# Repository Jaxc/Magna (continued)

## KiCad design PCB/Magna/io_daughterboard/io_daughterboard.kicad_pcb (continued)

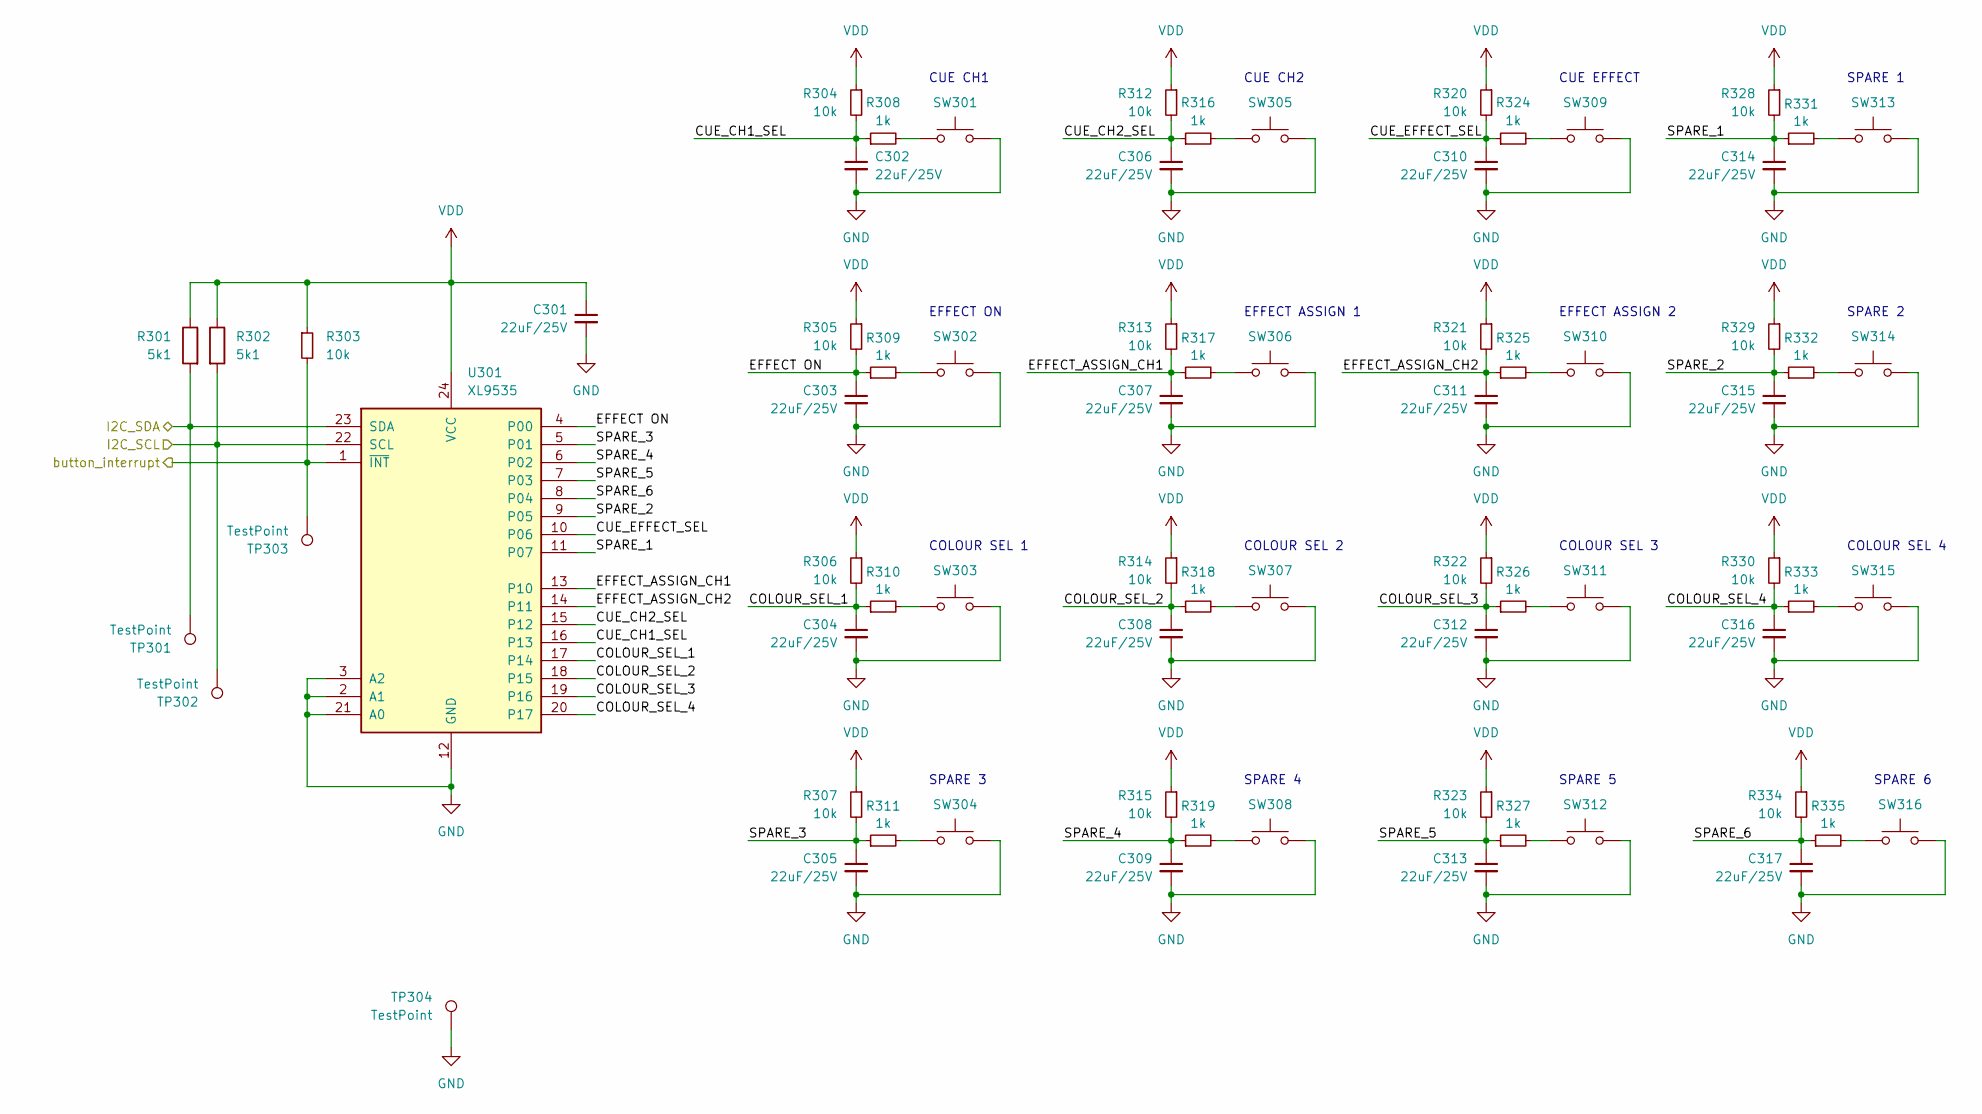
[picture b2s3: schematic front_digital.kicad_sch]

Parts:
C301, C302, C303, C304, C305, C306, C307, C308, C309, C310, C311, C312, C313, C314, C315, C316, C317: 22uF/25V; C_0805_2012Metric_Pad1.18x1.45mm_HandSolder; LCSC C45783
R301, R302: 5k1; R_0805_2012Metric_Pad1.20x1.40mm_HandSolder; LCSC C218638
R303, R304, R305, R306, R307, R312, R313, R314, R315, R320, R321, R322, R323, R328, R329, R330, R334: 10k; R_0805_2012Metric_Pad1.20x1.40mm_HandSolder; LCSC C17414
R308, R309, R310, R311, R316, R317, R318, R319, R324, R325, R326, R327, R331, R332, R333, R335: 1k; R_0805_2012Metric_Pad1.20x1.40mm_HandSolder; LCSC C17513
SW301, SW302, SW303, SW304, SW305, SW306, SW307, SW308, SW309, SW310, SW311, SW312, SW313, SW314, SW315, SW316: SW_Push_1P1T_XKB_TS-1187A; LCSC C318884
TP301, TP302, TP303, TP304: TestPoint; TestPoint_Keystone_5000-5004_Miniature
U301: XL9535; TSSOP-24_4.4x7.8mm_P0.65mm; LCSC C561273

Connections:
/Buttons/COLOUR_SEL_1: C304.1, R306.2, R310.1, U301.17 (P14)
/Buttons/COLOUR_SEL_2: C308.1, R314.2, R318.1, U301.18 (P15)
/Buttons/COLOUR_SEL_3: C312.1, R322.2, R326.1, U301.19 (P16)
/Buttons/COLOUR_SEL_4: C316.1, R330.2, R333.1, U301.20 (P17)
/Buttons/CUE_CH1_SEL: C302.1, R304.2, R308.1, U301.16 (P13)
/Buttons/CUE_CH2_SEL: C306.1, R312.2, R316.1, U301.15 (P12)
/Buttons/CUE_EFFECT_SEL: C310.1, R320.2, R324.1, U301.10 (P06)
/Buttons/EFFECT ON: C303.1, R305.2, R309.1, U301.4 (P00)
/Buttons/EFFECT_ASSIGN_CH1: C307.1, R313.2, R317.1, U301.13 (P10)
/Buttons/EFFECT_ASSIGN_CH2: C311.1, R321.2, R325.1, U301.14 (P11)
/Buttons/I2C_SCL: R302.2, TP302.1, U301.22 (SCL); also elsewhere on the board
/Buttons/I2C_SDA: R301.2, TP301.1, U301.23 (SDA); also elsewhere on the board
/Buttons/SPARE_1: C314.1, R328.2, R331.1, U301.11 (P07)
/Buttons/SPARE_2: C315.1, R329.2, R332.1, U301.9 (P05)
/Buttons/SPARE_3: C305.1, R307.2, R311.1, U301.5 (P01)
/Buttons/SPARE_4: C309.1, R315.2, R319.1, U301.6 (P02)
/Buttons/SPARE_5: C313.1, R323.2, R327.1, U301.7 (P03)
/Buttons/SPARE_6: C317.1, R334.2, R335.1, U301.8 (P04)
/Buttons/button_interrupt: R303.2, TP303.1, U301.1 (~INT); also elsewhere on the board
GND: C301.2, C302.2, C303.2, C304.2, C305.2, C306.2, C307.2, C308.2, C309.2, C310.2, C311.2, C312.2, C313.2, C314.2, C315.2, C316.2, C317.2, SW301.2, SW302.2, SW303.2, SW304.2, SW305.2, SW306.2, SW307.2, SW308.2, SW309.2, SW310.2, SW311.2, SW312.2, SW313.2, SW314.2, SW315.2, SW316.2, TP304.1, U301.2 (A1), U301.3 (A2), U301.12 (GND), U301.21 (A0); also elsewhere on the board
unnamed: R308.2, SW301.1
unnamed: R309.2, SW302.1
unnamed: R310.2, SW303.1
unnamed: R311.2, SW304.1
unnamed: R316.2, SW305.1
unnamed: R317.2, SW306.1
unnamed: R318.2, SW307.1
unnamed: R319.2, SW308.1
unnamed: R324.2, SW309.1
unnamed: R325.2, SW310.1
unnamed: R326.2, SW311.1
unnamed: R327.2, SW312.1
unnamed: R331.2, SW313.1
unnamed: R332.2, SW314.1
unnamed: R333.2, SW315.1
unnamed: R335.2, SW316.1
VDD: C301.1, R301.1, R302.1, R303.1, R304.1, R305.1, R306.1, R307.1, R312.1, R313.1, R314.1, R315.1, R320.1, R321.1, R322.1, R323.1, R328.1, R329.1, R330.1, R334.1, U301.24 (VCC); also elsewhere on the board

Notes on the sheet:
SPARE 2
CUE EFFECT
CUE CH2
EFFECT ASSIGN 1
COLOUR SEL 4
SPARE 1
SPARE 6
CUE CH1
COLOUR SEL 1
SPARE 4
COLOUR SEL 2
SPARE 3
COLOUR SEL 3
EFFECT ASSIGN 2
SPARE 5
EFFECT ON

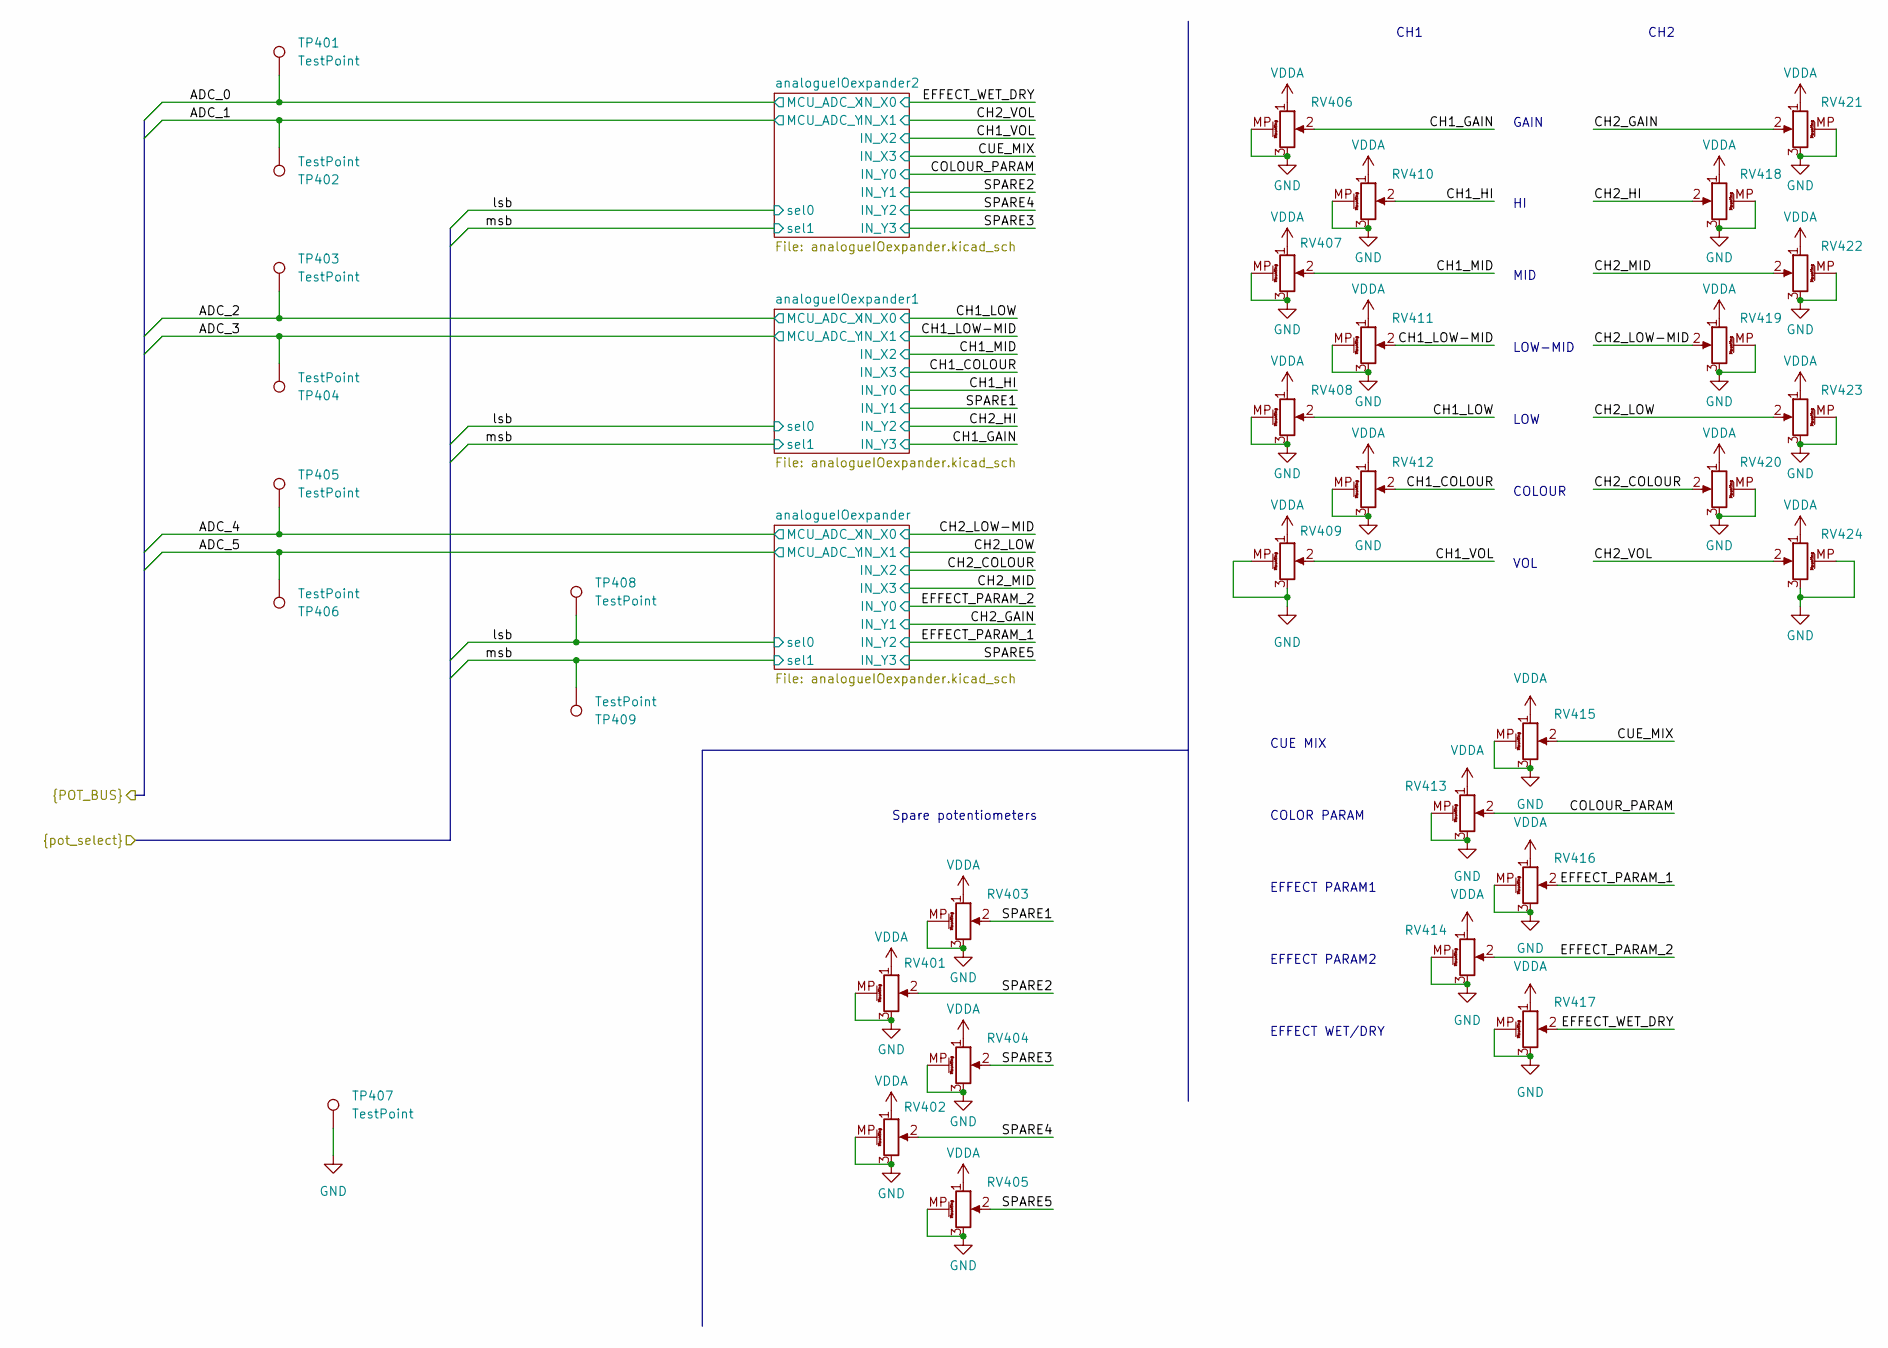
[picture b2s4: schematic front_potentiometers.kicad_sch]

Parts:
RV401, RV402, RV403, RV404, RV405, RV406, RV413, RV414, RV416, RV417, RV421: 10k/PTV09A-4030F-B103; Potentiometer_Bourns_PTV09A-1_Single_Vertical
RV407, RV408, RV410, RV411, RV412, RV418, RV419, RV420, RV422, RV423: 10k/PTV09A-4230F-B103; Potentiometer_Bourns_PTV09A-1_Single_Vertical
RV409, RV424: 10k/ PTA6043-2015DPB103; Potentiometer_Bourns_PTA6043_Single_Slide
RV415: 10k/PTV09A-2030F-B103; Potentiometer_Bourns_PTV1111415AB1103
TP401, TP402, TP403, TP404, TP405, TP406, TP407, TP408, TP409: TestPoint; TestPoint_Keystone_5000-5004_Miniature

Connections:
/Potentiometers/ADC_0: TP401.1; also elsewhere on the board
/Potentiometers/ADC_1: TP402.1; also elsewhere on the board
/Potentiometers/ADC_2: TP403.1; also elsewhere on the board
/Potentiometers/ADC_3: TP404.1; also elsewhere on the board
/Potentiometers/ADC_4: TP405.1; also elsewhere on the board
/Potentiometers/ADC_5: TP406.1; also elsewhere on the board
/Potentiometers/CH1_COLOUR: RV412.2; also elsewhere on the board
/Potentiometers/CH1_GAIN: RV406.2; also elsewhere on the board
/Potentiometers/CH1_HI: RV410.2; also elsewhere on the board
/Potentiometers/CH1_LOW: RV408.2; also elsewhere on the board
/Potentiometers/CH1_LOW-MID: RV411.2; also elsewhere on the board
/Potentiometers/CH1_MID: RV407.2; also elsewhere on the board
/Potentiometers/CH1_VOL: RV409.2; also elsewhere on the board
/Potentiometers/CH2_COLOUR: RV420.2; also elsewhere on the board
/Potentiometers/CH2_GAIN: RV421.2; also elsewhere on the board
/Potentiometers/CH2_HI: RV418.2; also elsewhere on the board
/Potentiometers/CH2_LOW: RV423.2; also elsewhere on the board
/Potentiometers/CH2_LOW-MID: RV419.2; also elsewhere on the board
/Potentiometers/CH2_MID: RV422.2; also elsewhere on the board
/Potentiometers/CH2_VOL: RV424.2; also elsewhere on the board
/Potentiometers/COLOUR_PARAM: RV413.2; also elsewhere on the board
/Potentiometers/CUE_MIX: RV415.2; also elsewhere on the board
/Potentiometers/EFFECT_PARAM_1: RV416.2; also elsewhere on the board
/Potentiometers/EFFECT_PARAM_2: RV414.2; also elsewhere on the board
/Potentiometers/EFFECT_WET_DRY: RV417.2; also elsewhere on the board
/Potentiometers/SPARE1: RV403.2; also elsewhere on the board
/Potentiometers/SPARE2: RV401.2; also elsewhere on the board
/Potentiometers/SPARE3: RV404.2; also elsewhere on the board
/Potentiometers/SPARE4: RV402.2; also elsewhere on the board
/Potentiometers/SPARE5: RV405.2; also elsewhere on the board
/Potentiometers/lsb: TP408.1; also elsewhere on the board
/Potentiometers/msb: TP409.1; also elsewhere on the board
GND: RV401.3, RV401.MP (MountPin), RV402.3, RV402.MP (MountPin), RV403.3, RV403.MP (MountPin), RV404.3, RV404.MP (MountPin), RV405.3, RV405.MP (MountPin), RV406.3, RV406.MP (MountPin), RV407.3, RV407.MP (MountPin), RV408.3, RV408.MP (MountPin), RV409.3, RV409.MP (MountPin), RV410.3, RV410.MP (MountPin), RV411.3, RV411.MP (MountPin), RV412.3, RV412.MP (MountPin), RV413.3, RV413.MP (MountPin), RV414.3, RV414.MP (MountPin), RV415.3, RV415.MP (MountPin), RV416.3, RV416.MP (MountPin), RV417.3, RV417.MP (MountPin), RV418.3, RV418.MP (MountPin), RV419.3, RV419.MP (MountPin), RV420.3, RV420.MP (MountPin), RV421.3, RV421.MP (MountPin), RV422.3, RV422.MP (MountPin), RV423.3, RV423.MP (MountPin), RV424.3, RV424.MP (MountPin), TP407.1; also elsewhere on the board
VDDA: RV401.1, RV402.1, RV403.1, RV404.1, RV405.1, RV406.1, RV407.1, RV408.1, RV409.1, RV410.1, RV411.1, RV412.1, RV413.1, RV414.1, RV415.1, RV416.1, RV417.1, RV418.1, RV419.1, RV420.1, RV421.1, RV422.1, RV423.1, RV424.1; also elsewhere on the board

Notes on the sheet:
COLOR PARAM
MID
Spare potentiometers
CH2
LOW-MID
VOL
GAIN
CH1
CUE MIX
LOW
EFFECT PARAM1
EFFECT PARAM2
COLOUR
EFFECT WET/DRY

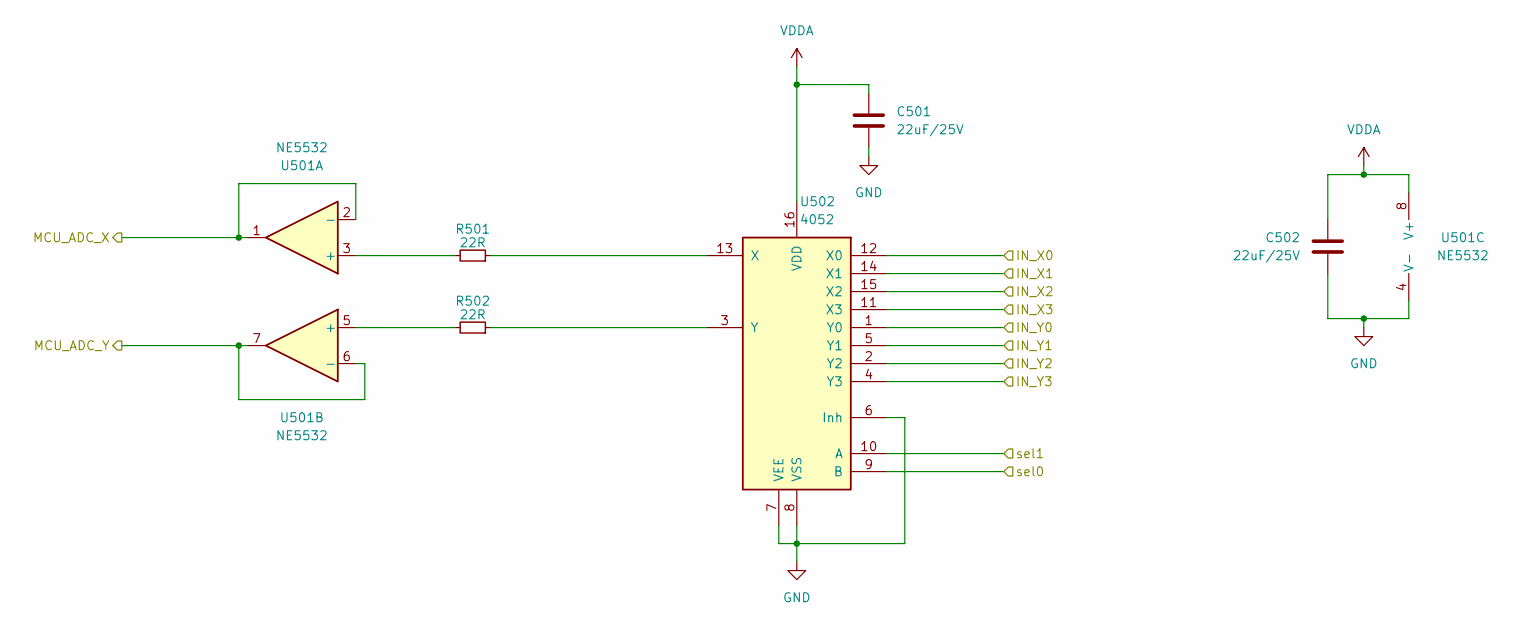
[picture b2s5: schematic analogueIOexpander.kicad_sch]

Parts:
C501, C502: 22uF/25V; C_0805_2012Metric_Pad1.18x1.45mm_HandSolder; LCSC C45783
R501, R502: 22R; R_0805_2012Metric_Pad1.20x1.40mm_HandSolder; LCSC C17561
U501: NE5532; SOIC-8_3.9x4.9mm_P1.27mm; LCSC C7426
U502: 4052; SOIC-16_3.9x9.9mm_P1.27mm; LCSC C6521

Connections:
/Potentiometers/ADC_0: U501.1, U501.2 (-); also elsewhere on the board
/Potentiometers/ADC_1: U501.6 (-), U501.7; also elsewhere on the board
/Potentiometers/CH1_VOL: U502.15 (X2); also elsewhere on the board
/Potentiometers/CH2_VOL: U502.14 (X1); also elsewhere on the board
/Potentiometers/COLOUR_PARAM: U502.1 (Y0); also elsewhere on the board
/Potentiometers/CUE_MIX: U502.11 (X3); also elsewhere on the board
/Potentiometers/EFFECT_WET_DRY: U502.12 (X0); also elsewhere on the board
/Potentiometers/SPARE2: U502.5 (Y1); also elsewhere on the board
/Potentiometers/SPARE3: U502.4 (Y3); also elsewhere on the board
/Potentiometers/SPARE4: U502.2 (Y2); also elsewhere on the board
/Potentiometers/lsb: U502.9 (B); also elsewhere on the board
/Potentiometers/msb: U502.10 (A); also elsewhere on the board
GND: C501.2, C502.2, U501.4 (V-), U502.6 (Inh), U502.7 (VEE), U502.8 (VSS); also elsewhere on the board
unnamed: R501.2, U501.3 (+)
unnamed: R502.2, U501.5 (+)
unnamed: R501.1, U502.13 (X)
unnamed: R502.1, U502.3 (Y)
VDDA: C501.1, C502.1, U501.8 (V+), U502.16 (VDD); also elsewhere on the board

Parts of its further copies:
C601, C602, C701, C702: 22uF/25V; C_0805_2012Metric_Pad1.18x1.45mm_HandSolder; LCSC C45783
R601, R602, R701, R702: 22R; R_0805_2012Metric_Pad1.20x1.40mm_HandSolder; LCSC C17561
U601, U701: NE5532; SOIC-8_3.9x4.9mm_P1.27mm; LCSC C7426
U602, U702: 4052; SOIC-16_3.9x9.9mm_P1.27mm; LCSC C6521

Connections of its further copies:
/Potentiometers/ADC_2: U601.1, U601.2 (-); also elsewhere on the board
/Potentiometers/ADC_3: U601.6 (-), U601.7; also elsewhere on the board
/Potentiometers/ADC_4: U701.1, U701.2 (-); also elsewhere on the board
/Potentiometers/ADC_5: U701.6 (-), U701.7; also elsewhere on the board
/Potentiometers/CH1_COLOUR: U602.11 (X3); also elsewhere on the board
/Potentiometers/CH1_GAIN: U602.4 (Y3); also elsewhere on the board
/Potentiometers/CH1_HI: U602.1 (Y0); also elsewhere on the board
/Potentiometers/CH1_LOW: U602.12 (X0); also elsewhere on the board
/Potentiometers/CH1_LOW-MID: U602.14 (X1); also elsewhere on the board
/Potentiometers/CH1_MID: U602.15 (X2); also elsewhere on the board
/Potentiometers/CH2_COLOUR: U702.15 (X2); also elsewhere on the board
/Potentiometers/CH2_GAIN: U702.5 (Y1); also elsewhere on the board
/Potentiometers/CH2_HI: U602.2 (Y2); also elsewhere on the board
/Potentiometers/CH2_LOW: U702.14 (X1); also elsewhere on the board
/Potentiometers/CH2_LOW-MID: U702.12 (X0); also elsewhere on the board
/Potentiometers/CH2_MID: U702.11 (X3); also elsewhere on the board
/Potentiometers/EFFECT_PARAM_1: U702.2 (Y2); also elsewhere on the board
/Potentiometers/EFFECT_PARAM_2: U702.1 (Y0); also elsewhere on the board
/Potentiometers/SPARE1: U602.5 (Y1); also elsewhere on the board
/Potentiometers/SPARE5: U702.4 (Y3); also elsewhere on the board
/Potentiometers/lsb: U602.9 (B), U702.9 (B); also elsewhere on the board
/Potentiometers/msb: U602.10 (A), U702.10 (A); also elsewhere on the board
GND: C601.2, C602.2, C701.2, C702.2, U601.4 (V-), U602.6 (Inh), U602.7 (VEE), U602.8 (VSS), U701.4 (V-), U702.6 (Inh), U702.7 (VEE), U702.8 (VSS); also elsewhere on the board
unnamed: R601.2, U601.3 (+)
unnamed: R602.2, U601.5 (+)
unnamed: R601.1, U602.13 (X)
unnamed: R602.1, U602.3 (Y)
unnamed: R701.2, U701.3 (+)
unnamed: R702.2, U701.5 (+)
unnamed: R701.1, U702.13 (X)
unnamed: R702.1, U702.3 (Y)
VDDA: C601.1, C602.1, C701.1, C702.1, U601.8 (V+), U602.16 (VDD), U701.8 (V+), U702.16 (VDD); also elsewhere on the board

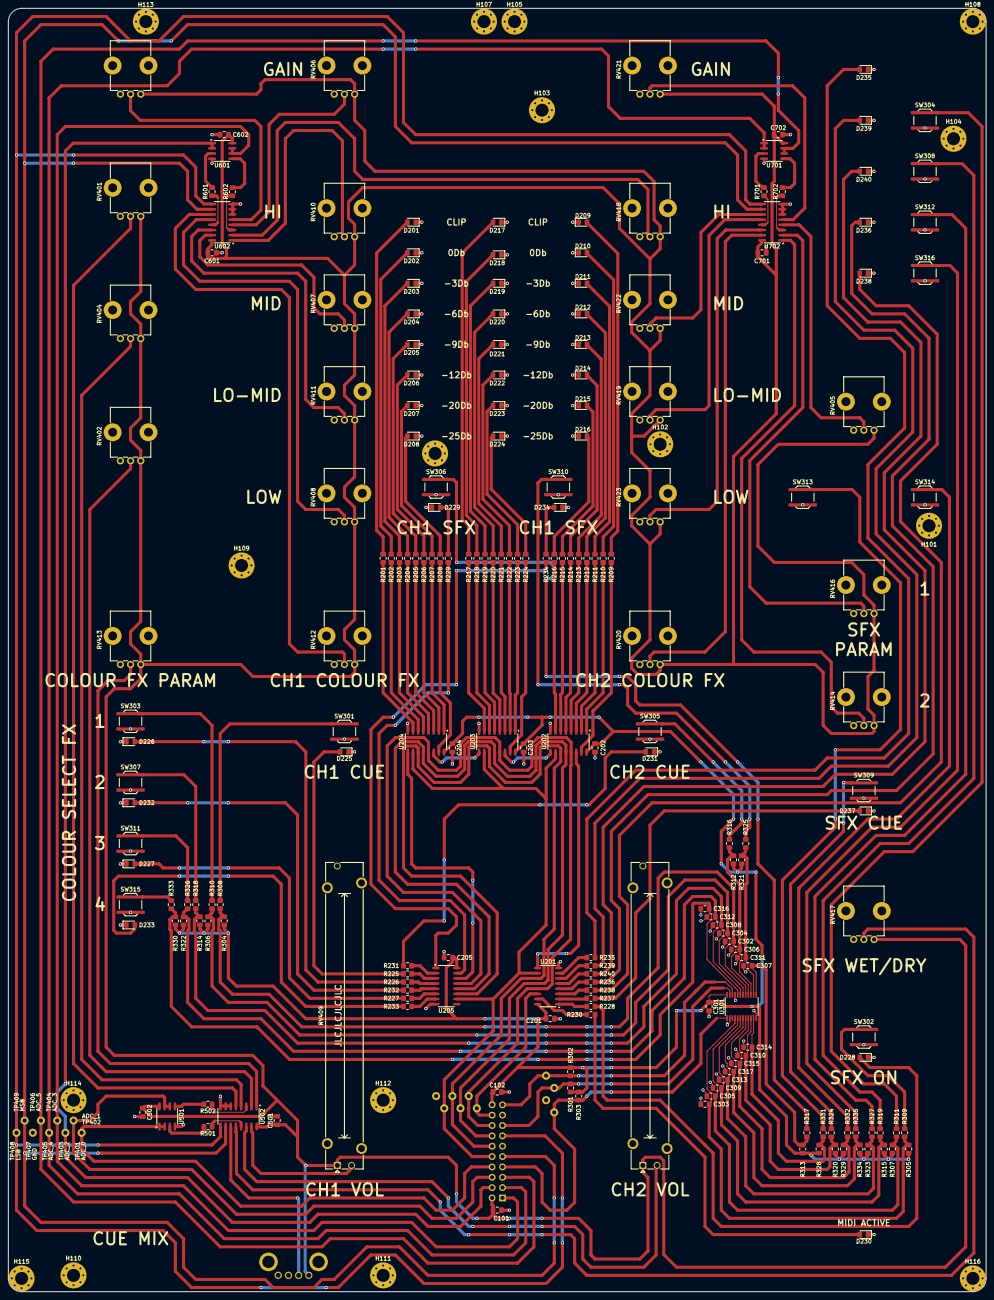
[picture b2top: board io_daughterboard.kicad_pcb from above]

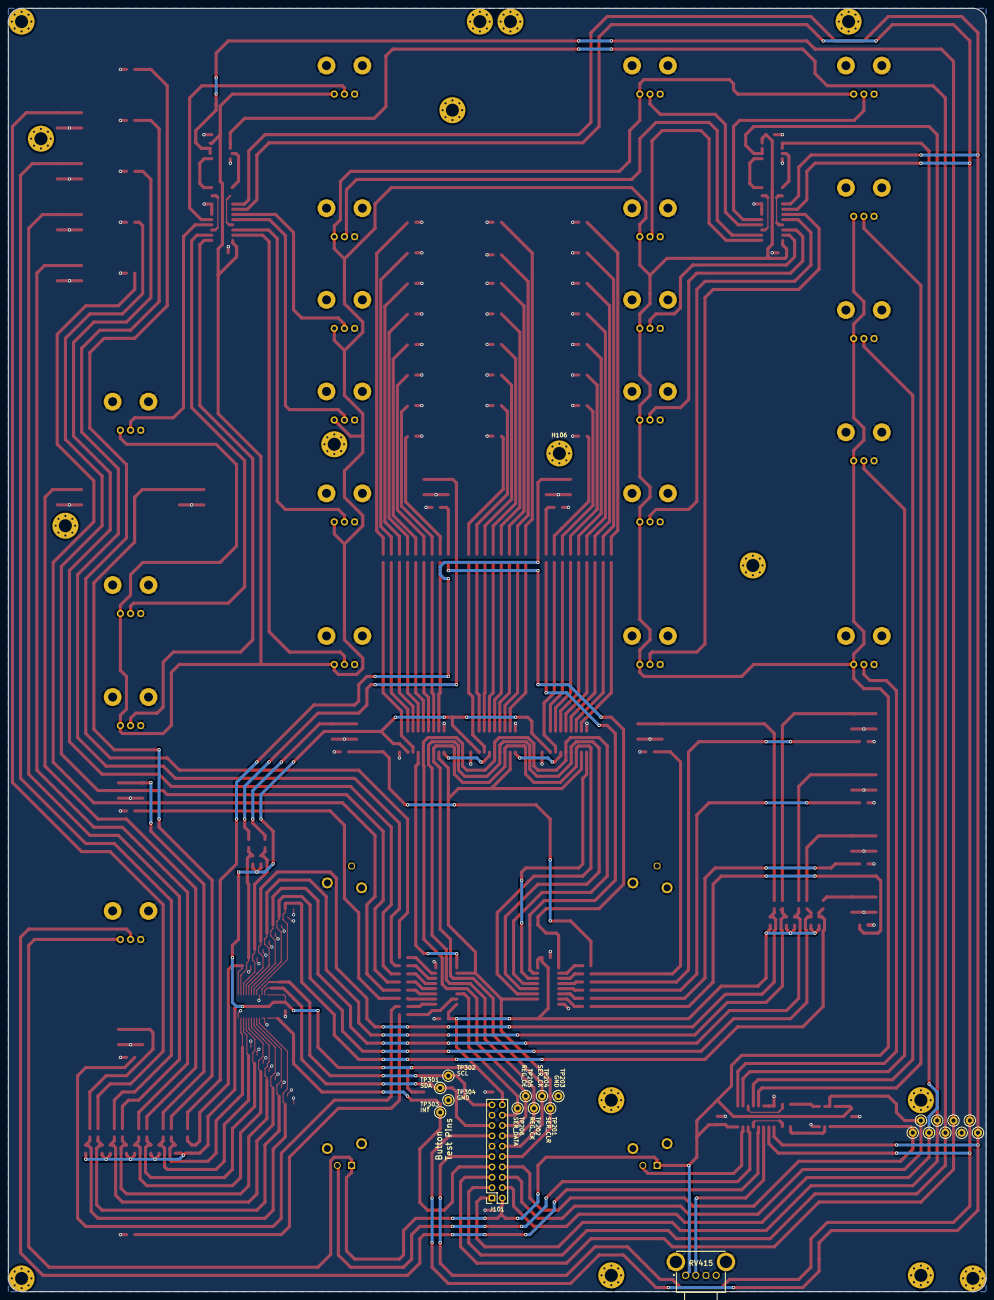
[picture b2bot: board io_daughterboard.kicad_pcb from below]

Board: 2 copper layers, 240.0 x 315.0 mm, 239 parts (21 on the bottom side), 171 nets.

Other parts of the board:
H115, H116: MountingHole_Pad; MountingHole_3.2mm_M3_Pad_Via

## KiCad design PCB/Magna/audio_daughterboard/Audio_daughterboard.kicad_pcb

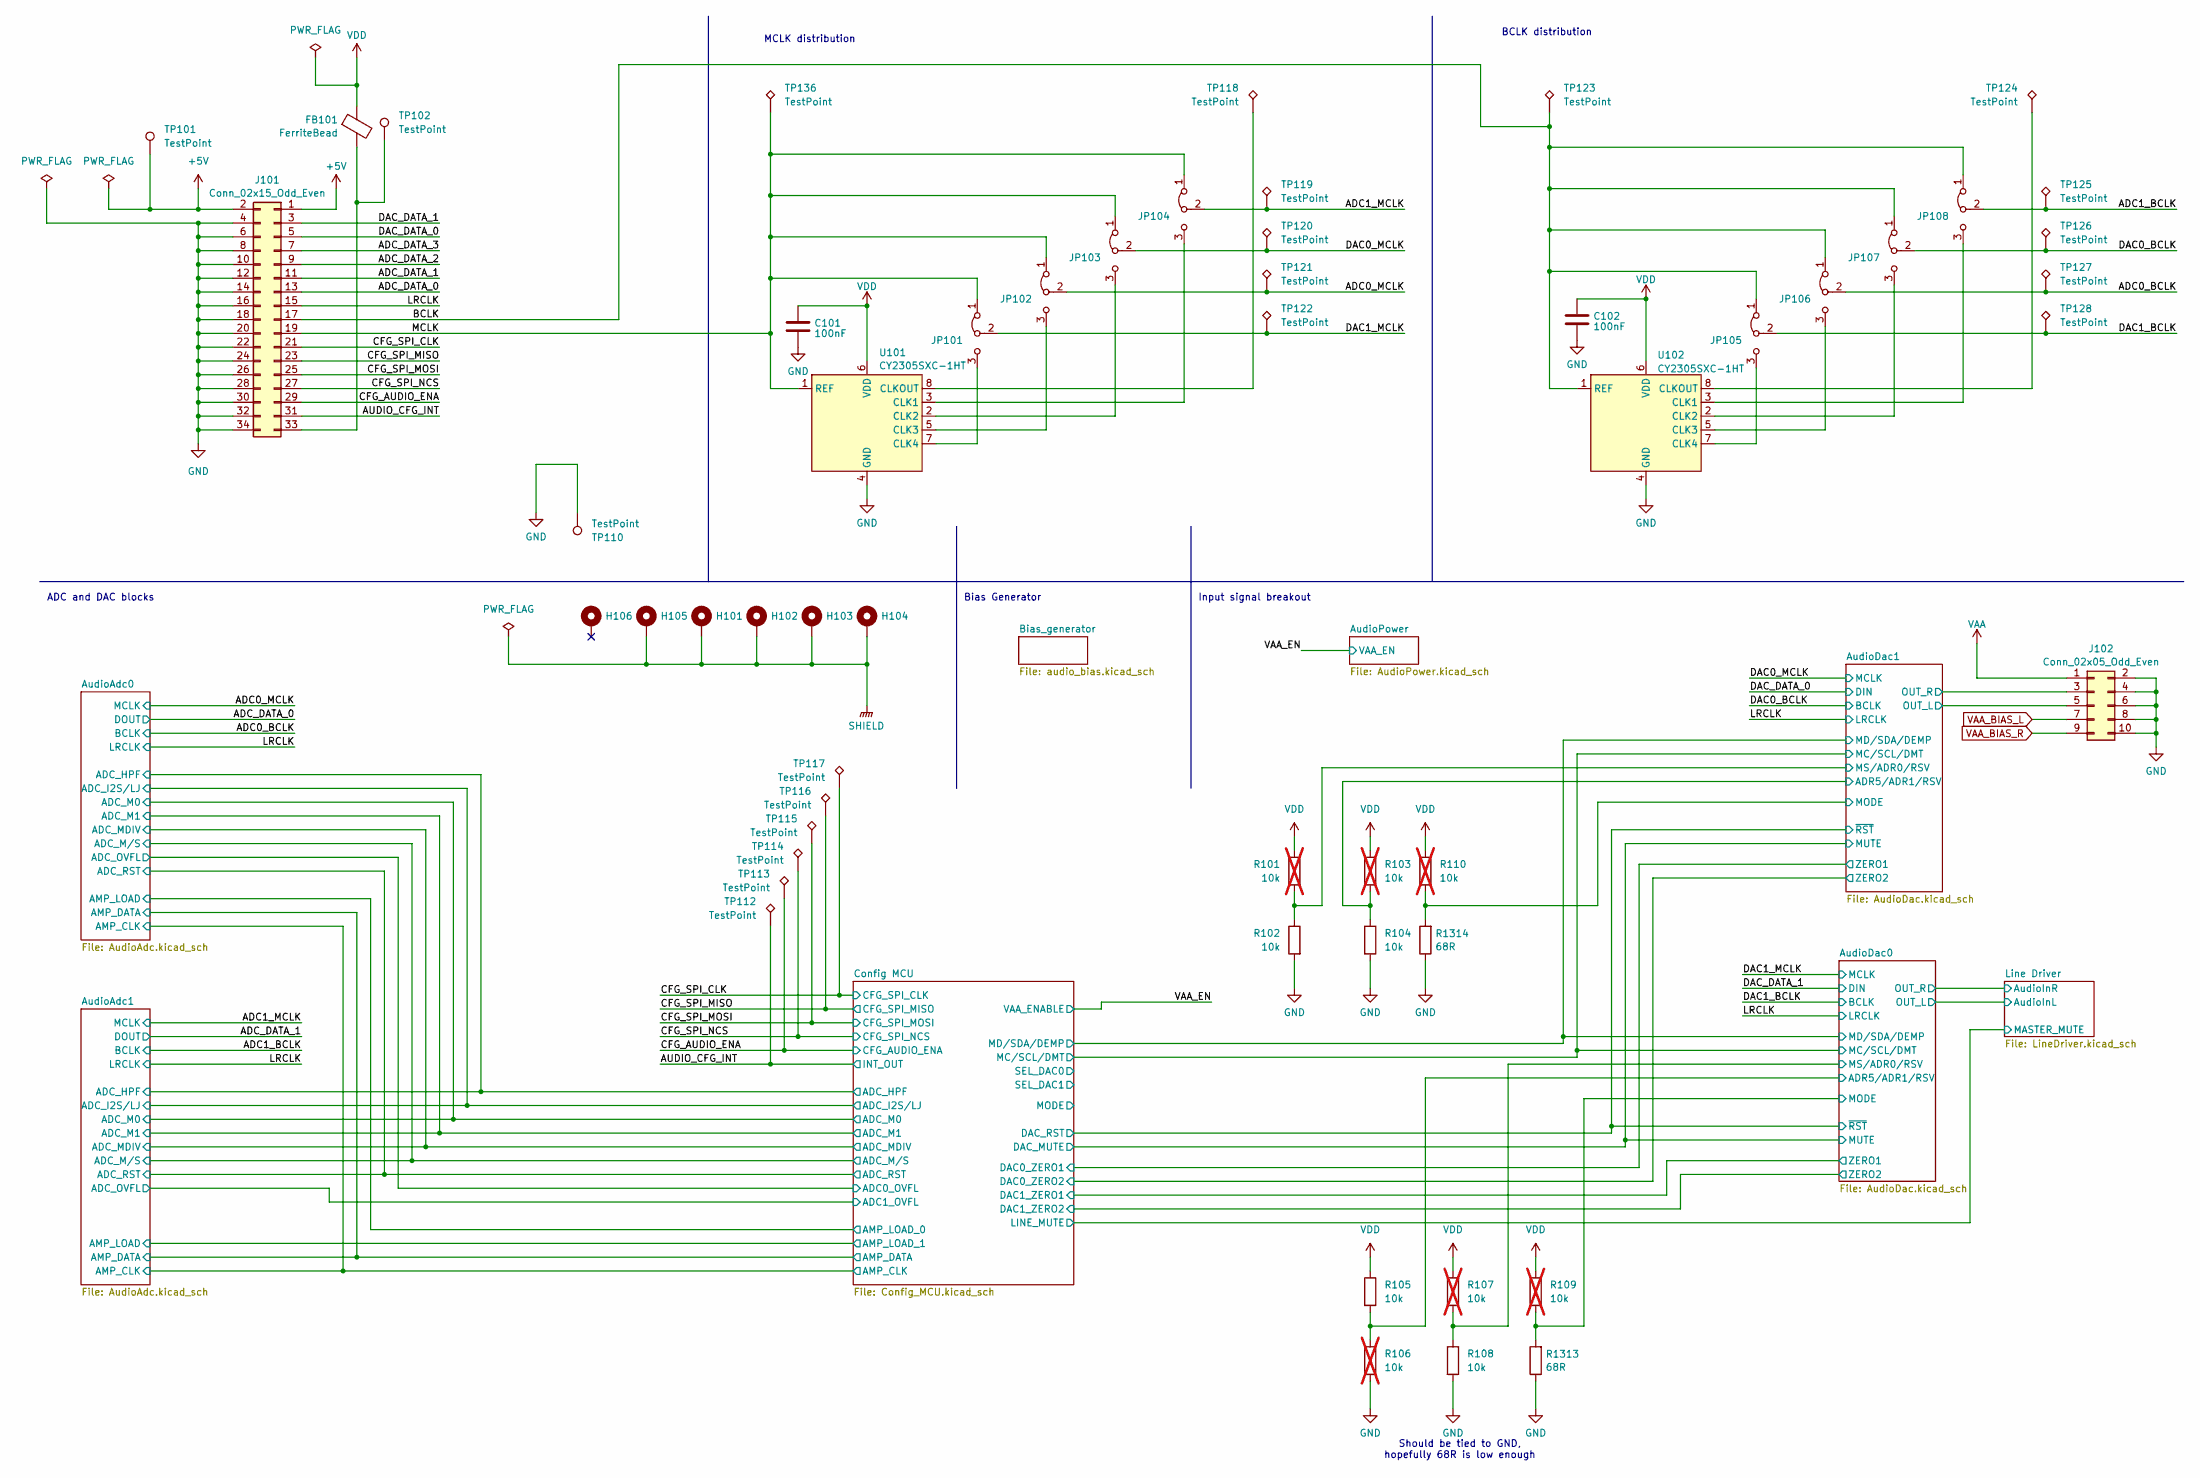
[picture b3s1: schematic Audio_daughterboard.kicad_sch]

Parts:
C101, C102: 100nF; C_0603_1608Metric; LCSC C14663
FB101: FerriteBead; L_0805_2012Metric; LCSC C1015
H101, H102, H103, H104, H105, H106: MountingHole_Pad; MountingHole_3.2mm_M3_Pad_Via
J101: Conn_02x15_Odd_Even; PinHeader_2x17_P2.54mm_Horizontal
J102: Conn_02x05_Odd_Even; PinHeader_2x05_P2.54mm_Horizontal
JP101, JP102, JP103, JP104, JP105, JP106, JP107, JP108: Jumper_3_Bridged12; SolderJumper-3_P1.3mm_Bridged12_RoundedPad1.0x1.5mm_NumberL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
R101, R103, R106, R107, R109, R110: 10k; R_0603_1608Metric; LCSC C95204; not fitted
R102, R104, R105, R108: 10k; R_0603_1608Metric; LCSC C95204
R1313, R1314: 68R; R_0603_1608Metric; LCSC C351632
TP101, TP102, TP110: TestPoint; TestPoint_Keystone_5005-5009_Compact
TP112, TP113, TP114, TP115, TP116, TP117, TP118, TP119, TP120, TP121, TP122, TP123, TP124, TP125, TP126, TP127, TP128, TP136: TestPoint; TestPoint_Pad_1.0x1.0mm
U101, U102: CY2305SXC-1HT; SOIC-8_3.9x4.9mm_P1.27mm; LCSC C914887

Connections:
+5V: J101.1, J101.2, TP101.1; also elsewhere on the board
/ADC0_BCLK: JP106.2 (C), TP127.1; also elsewhere on the board
/ADC0_MCLK: JP102.2 (C), TP121.1; also elsewhere on the board
/ADC1_BCLK: JP108.2 (C), TP125.1; also elsewhere on the board
/ADC1_MCLK: JP104.2 (C), TP119.1; also elsewhere on the board
/ADC_DATA_0: J101.13; also elsewhere on the board
/ADC_DATA_1: J101.11; also elsewhere on the board
/ADC_DATA_2: J101.9
/ADC_DATA_3: J101.7
/AUDIO_CFG_INT: J101.31, TP112.1; also elsewhere on the board
/AudioDac0/ADR5/ADR1/RSV: R105.2, R106.1; also elsewhere on the board
/AudioDac0/MODE: R109.2, R1313.2; also elsewhere on the board
/AudioDac0/MS/ADR0/RSV: R107.2, R108.1; also elsewhere on the board
/AudioDac1/ADR5/ADR1/RSV: R103.2, R104.1; also elsewhere on the board
/AudioDac1/MODE: R110.2, R1314.2; also elsewhere on the board
/AudioDac1/MS/ADR0/RSV: R101.2, R102.1; also elsewhere on the board
/AudioDac1/OUT_L: J102.5; also elsewhere on the board
/AudioDac1/OUT_R: J102.3; also elsewhere on the board
/BCLK: J101.17, JP105.1 (A), JP106.1 (A), JP107.1 (A), JP108.1 (A), TP123.1, U102.1 (REF)
/CFG_AUDIO_ENA: J101.29, TP113.1; also elsewhere on the board
/CFG_SPI_CLK: J101.21, TP117.1; also elsewhere on the board
/CFG_SPI_MISO: J101.23, TP116.1; also elsewhere on the board
/CFG_SPI_MOSI: J101.25, TP115.1; also elsewhere on the board
/CFG_SPI_NCS: J101.27, TP114.1; also elsewhere on the board
/DAC0_BCLK: JP107.2 (C), TP126.1; also elsewhere on the board
/DAC0_MCLK: JP103.2 (C), TP120.1; also elsewhere on the board
/DAC1_BCLK: JP105.2 (C), TP128.1; also elsewhere on the board
/DAC1_MCLK: JP101.2 (C), TP122.1; also elsewhere on the board
/DAC_DATA_0: J101.5; also elsewhere on the board
/DAC_DATA_1: J101.3; also elsewhere on the board
/LRCLK: J101.15; also elsewhere on the board
/MCLK: J101.19, JP101.1 (A), JP102.1 (A), JP103.1 (A), JP104.1 (A), TP136.1, U101.1 (REF)
GND: C101.2, C102.2, J101.4, J101.6, J101.8, J101.10, J101.12, J101.14, J101.16, J101.18, J101.20, J101.22, J101.24, J101.26, J101.28, J101.30, J101.32, J101.34, J102.2, J102.4, J102.6, J102.8, J102.10, R102.2, R104.2, R106.2, R108.2, R1313.1, R1314.1, TP110.1, U101.4 (GND), U102.4 (GND); also elsewhere on the board
unnamed: FB101.2, J101.33, TP102.1
unnamed: JP101.3 (B), U101.7 (CLK4)
unnamed: JP102.3 (B), U101.5 (CLK3)
unnamed: JP103.3 (B), U101.2 (CLK2)
unnamed: JP104.3 (B), U101.3 (CLK1)
unnamed: JP105.3 (B), U102.7 (CLK4)
unnamed: JP106.3 (B), U102.5 (CLK3)
unnamed: JP107.3 (B), U102.2 (CLK2)
unnamed: JP108.3 (B), U102.3 (CLK1)
unnamed: TP118.1, U101.8 (CLKOUT)
unnamed: TP124.1, U102.8 (CLKOUT)
SHIELD: H101.1, H102.1, H103.1, H104.1, H105.1
VAA: J102.1; also elsewhere on the board
VAA_BIAS_L: J102.7; also elsewhere on the board
VAA_BIAS_R: J102.9; also elsewhere on the board
VDD: C101.1, C102.1, FB101.1, R101.1, R103.1, R105.1, R107.1, R109.1, R110.1, U101.6 (VDD), U102.6 (VDD); also elsewhere on the board

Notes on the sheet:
Bias Generator
Should be tied to GND, hopefully 68R is low enough
MCLK distribution
ADC and DAC blocks
Input signal breakout
BCLK distribution
